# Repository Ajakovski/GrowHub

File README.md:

<div align="center">

# GrowHub - Vertical Garden

### _A highly efficient vertical plant growing garden with AI controlls for user-free handling experience._ 
  
</div>

---

# Overview

***GrowHub - Vertical Garden***

A sophisticated way of growing whatever kind of plant (only legal ones :}) from your living room, balcony, even your bedroom or wherever you want!

The idea of the project is to have a care-free environment where the user only monitors his plants from the website and we the developers are resposnible for making everything functional for healthy and low-cost plant growing.

It is a modular garden capable of supplying 1-3 floors of growing area split between 8 tiles per floor!!!

With a good team we managed to split the 4 main segments of this project accordingly which are: PCB and electrical construction, mechanical functioning of the project, server control, User-friendly and work-free experience for the customers.

---

# Motivation

In todays world a lot more people are living in flats and with the constant inflation plus the enforcment of consuming lab products a lot of people are getting restrained of consuming real, healthy and natural food.

The soil is constantly polluted due to new construction working and the constant droughts are limiting the farmers to produce enough single-ingredient food for the families in the metropolitan cities.

With those issues on mind me and my friend have come up with an idea to revolutionize the way people are getting natural ingreidents in their households.

The main goals that we want to achieve are the following:

- User-friendly and work-free experience for anyone having this product
- Highly efficiency for growing plants
- Healthy environment for both the plants and users

A lot of working skills are required for this project to succeed so i hope you understand our issues with shipping functional projects in Week 1.

---

# BOM

*Some modules are dependant based on the amount of floors accounted in the project (1-3)

_Everything is calculated for the highest amount of floors - 3_

_M = main board (×1) · F = floor board (×3) · Qty = M + 3 × F. Capacitors with no voltage listed sit on ≤ 5 V nets. Resistors are 1 % thick film, 0603 = 0.1 W, unless noted. DNP footprints and test pads are not listed._

| Designator | Function | Part | Package | Qty (3 floors) | Unit (USD) | Total (USD) | Link |
|---|---|---|---|---:|---:|---:|---|
| M: U6 | MCU module, Wi-Fi/BLE (16 MB flash, 8 MB PSRAM, U.FL antenna) | ESP32-S3-WROOM-1U-N16R8 | SMD module | 1 | $6.90 | $6.90 | [Mouser](https://www.mouser.com/en/ProductDetail/Espressif-Systems/ESP32-S3-WROOM-1U-N16R8?qs=Li%252BoUPsLEns6V0Pr5KRJtw%3D%3D) |
| M: U1 | USB D+/D− ESD protection | USBLC6-2P6 | SOT-666 | 1 | $0.65 | $0.65 | [Mouser](https://www.mouser.com/en/ProductDetail/STMicroelectronics/USBLC6-2P6?qs=6ARB0lp6jlViGcbUSvj1Mw%3D%3D) |
| M: U2 | Ambient light sensor | VEML7700-TT | SMD, 4-pin | 1 | $1.35 | $1.35 | [Mouser](https://www.mouser.com/en/ProductDetail/Vishay-Semiconductors/VEML7700-TT?qs=BcfjnG7NVaXdL6DJFdWbdw%3D%3D) |
| M: U3 | Load-cell ADC (tank mass) | NAU7802SGI | SOIC-16 | 1 | $1.87 | $1.87 | [Mouser](https://www.mouser.com/en/ProductDetail/Nuvoton/NAU7802SGI?qs=A6eO%252BMLsxmSrxisJRahwRQ%3D%3D) |
| M: U4 | Valve rail switch, current-limited | TPS27S100BPWPR | HTSSOP-14 | 1 | $3.04 | $3.04 | [Mouser](https://www.mouser.com/en/ProductDetail/Texas-Instruments/TPS27S100BPWPR?qs=0lQeLiL1qyaF4011Zes0Yg%3D%3D) |
| M: U5, U7, U9 | Floor-cable I²C buffers | PCA9600DPZ | TSSOP-8 | 3 | $6.80 | $20.40 | [Mouser](https://www.mouser.com/en/ProductDetail/NXP-Semiconductors/PCA9600DPZ?qs=Li%252BoUPsLEnu5vr2lXlgE1A%3D%3D) |
| M: U8 | Surge stopper + reverse blocking | LTC4364IS-2#PBF | SOIC-16 | 1 | $14.82 | $14.82 | [Mouser](https://www.mouser.com/en/ProductDetail/Analog-Devices/LTC4364IS-2PBF?qs=hVkxg5c3xu9riE%252B4zWkG8g%3D%3D) |
| M: U10 | Buck, 24 V → 5 V | LMR33630ADDA | HSOP-8 (exposed pad) | 1 | $3.67 | $3.67 | [Mouser](https://www.mouser.com/en/ProductDetail/Texas-Instruments/LMR33630ADDA?qs=r5DSvlrkXmL3yj62Sna%2FpQ%3D%3D) |
| M: U11 | Input current / power monitor | INA226AIDGSR | VSSOP-10 | 1 | $2.75 | $2.75 | [Mouser](https://www.mouser.com/en/ProductDetail/Texas-Instruments/INA226AIDGSR?qs=tQG3bEuiOZD4quG3egR36g%3D%3D) |
| M: U12 | Floor bus switch (I²C mux) | TCA9548APWR | TSSOP-24 | 1 | $1.65 | $1.65 | [Mouser](https://www.mouser.com/en/ProductDetail/Texas-Instruments/TCA9548APWR?qs=sGAEpiMZZMutXGli8Ay4kHAf4%2FN1WW693xDAZd3LyqA%3D) |
| F: U13 | Temperature & humidity (PTFE filter membrane) | SHT40I-AD1F-R2 | DFN-4, 1.5 × 1.5 mm | 3 | $3.06 | $9.18 | [Mouser](https://www.mouser.com/ProductDetail/Sensirion/SHT40I-AD1F-R2?qs=rQFj71Wb1eVYLTRlLwJKVQ%3D%3D) |
| F: U14, U17 | 3.3 V LDOs: logic (U17), switched sensor rail (U14) | TPS7A2033PDBVR | SOT-23-5 | 6 | $0.37 | $2.22 | [Mouser](https://www.mouser.com/en/ProductDetail/Texas-Instruments/TPS7A2033PDBVR?qs=hd1VzrDQEGjk%2FOBnRfKB4A%3D%3D) |
| F: U16 | Tray-electrode ADC | ADS1115IDGSR | VSSOP-10 | 3 | $5.19 | $15.57 | [Mouser](https://www.mouser.com/en/ProductDetail/Texas-Instruments/ADS1115IDGSR?qs=IK5e5L0zOXjKCJoVMhYO%2FQ%3D%3D) |
| F: U18 | Floor ID (1-Wire EEPROM) | DS28E07Q+T | TDFN-6, 3 × 3 mm | 3 | $2.31 | $6.93 | [Mouser](https://www.mouser.com/ProductDetail/Maxim-Integrated/DS28E07Q+T?qs=kmv/Ww32SUN5PBVtaB9uEw%3D%3D) |
| F: U19 | PWM: 4 LED channels + tray excitation | PCA9685PW,118 | TSSOP-28  (board has HVQFN-28) | 3 | $4.02 | $12.06 | [Mouser](https://www.mouser.com/ProductDetail/NXP-Semiconductors/PCA9685PW118?qs=6YAT8rHPFU%2BtfwwKq4nwEQ%3D%3D) |
| F: U20 | Floor-end cable buffer | P82B96TD,118 (NXP) | SOIC-8 | 3 | $6.15 | $18.45 | [Mouser](https://www.mouser.com/ProductDetail/NXP-Semiconductors/P82B96TD118/?qs=LOCUfHb8d9vV76HkGf93IA%3D%3D) |
| M: C11 | Load-cell ADC, VIN2P–VIN2N | C0603C331J5GACTU (330 pF, 50 V, C0G) | 0603 | 1 | $0.11 | $0.11 | [Mouser](https://www.mouser.com/c/?q=C0603C331J5GACTU) |
| M: C19 | Valve current-monitor filter | 06031F102K4T2A (1 nF, 100 V, X8R) | 0603 | 1 | $0.19 | $0.19 | [Mouser](https://www.mouser.com/en/ProductDetail/KYOCERA-AVX/06031F102K4T2A?qs=%252BdQmOuGyFcFZxL9GWikwcQ%3D%3D) |
| M: C24 | Valve-switch input, 24 V | C0603C472K5RACTU (4.7 nF, 50 V, X7R) | 0603 | 1 | $0.11 | $0.11 | [Mouser](https://www.mouser.com/c/?q=C0603C472K5RACTU) |
| M: C4, C6, C16, C18, C20, C57<br>F: C56, C64 | ADC / input filters | C0603C103K5RACTU (10 nF, 50 V, X7R) | 0603 | 12 | $0.068 | $0.82 | [Mouser](https://www.mouser.com/c/?q=C0603C103K5RACTU) |
| M: C25 | Valve rail output, 24 V | C0603C223K5RACTU (22 nF, 50 V, X7R) | 0603 | 1 | $0.12 | $0.12 | [Mouser](https://www.mouser.com/c/?q=C0603C223K5RACTU) |
| M: C13, C34, C40 | IO0 boot RC (C13), surge-stopper timer (C34), gate RC (C40) | C0603C473K1RACTU (47 nF, 100 V, X7R) | 0603 | 3 | $0.51 | $1.53 | [Mouser](https://www.mouser.com/c/?q=C0603C473K1RACTU) |
| M: C1, C5, C7, C10, C12, C15, C17, C22, C26–C28, C35, C37, C47–C50, C79–C81, C83, C84<br>F: C58, C59, C68, C70, C72, C77, C78, C85 | Decoupling, incl. the 24 V rails | C0603C104K5RACTU (100 nF, 50 V, X7R) | 0603 | 46 | $0.09 | $4.14 | [Mouser](https://www.mouser.com/c/?q=C0603C104K5RACTU) |
| M: C30, C43 | VIN / surge-stopper supply | C0805C104K1RACTU (100 nF, 100 V, X7R) | 0805 | 2 | $0.32 | $0.64 | [Mouser](https://www.mouser.com/c/?q=C0805C104K1RACTU) |
| M: C23, C32, C45 | Buck / valve-switch input caps | C0603C224K5RACTU (220 nF, 50 V, X7R) | 0603 | 3 | $0.44 | $1.32 | [Mouser](https://www.mouser.com/c/?q=C0603C224K5RACTU) |
| M: C2, C9, C14, C33, C46<br>F: C55, C60, C65, C67, C69, C71 | Decoupling / regulator VCC | C1608X7R1H105K080AB (1 µF, 50 V, X7R) | 0603 | 23 | $0.141 | $3.24 | [Mouser](https://www.mouser.com/c/?q=C1608X7R1H105K080AB) |
| F: C75, C76 | Floor 24 V entry | C0805C105K5RACTU (1 µF, 50 V, X7R) | 0805 | 6 | $0.66 | $3.96 | [Mouser](https://www.mouser.com/c/?q=C0805C105K5RACTU) |
| M: C31 | 5 V buck input, 24 V | C1210C475K5RACTU (4.7 µF, 50 V, X7R) | 1210 | 1 | $1.27 | $1.27 | [Mouser](https://www.mouser.com/c/?q=C1210C475K5RACTU) |
| M: C8, C44<br>F: C21 | Bulk, 3.3 / 5 V | C2012X7S1E106K125AE (10 µF, 25 V, X7S) | 0805 | 5 | $0.81 | $4.05 | [Mouser](https://www.mouser.com/c/?q=C2012X7S1E106K125AE) |
| M: C82 | Bulk, debug LEDs (5 V) | C1206C106K3RACTU (10 µF, 25 V, X7R) | 1206 | 1 | $1.63 | $1.63 | [Mouser](https://www.mouser.com/c/?q=C1206C106K3RACTU) |
| M: C29 | 5 V buck input, 24 V | C1210C106K5RACTU (10 µF, 50 V, X7R) | 1210 | 1 | $1.92 | $1.92 | [Mouser](https://www.mouser.com/c/?q=C1210C106K5RACTU) |
| M: C3, C38, C39, C41, C42, C51–C54 | Buck outputs, 3.3 / 5 V | CL31A226KAHNNNE (22 µF, 25 V, X5R) | 1206 | 9 | $0.81 | $7.29 | [Mouser](https://www.mouser.com/c/?q=CL31A226KAHNNNE) |
| M: C36<br>F: C73, C74 | Bulk, 24 V rail | MAL215097102E3 (220 µF, 50 V, 150 CRZ) | SMD can, 10 × 10 mm base, 17 mm tall | 7 | $2.63 | $18.41 | [Mouser](https://www.mouser.com/en/ProductDetail/Vishay-BC-Components/MAL215097102E3?qs=qmStTZH4TznNa7zgwdGJWg%3D%3D) |
| M: D1, D2, D5–D7, D17, D18, D39, D40, D42, D43<br>F: D24–D26, D45 | ESD, 3.3 V lines (load cell, leak, float, tray, OE, nRESET) | ESD5Z3.3T1G | SOD-523 | 23 | $0.144 | $3.31 | [Mouser](https://www.mouser.com/en/ProductDetail/onsemi/ESD5Z3.3T1G?qs=OSf9jACorvaH3Y8oRWEcuQ%3D%3D) |
| M: D3<br>F: D30, D31 | Pump flyback (D3), LED channel flybacks (D30, D31) | B360A-13-F (60 V, 3 A) | SMA (DO-214AC) | 7 | $0.54 | $3.78 | [Mouser](https://www.mouser.com/ProductDetail/Diodes-Incorporated/B360A-13-F?qs=sVoUGXYOGv3xoCWNHVb4bA%3D%3D) |
| M: D4, D37, D38 | Debug LEDs | Adafruit 1655 (SK6812 5050, 10-pack) | 5050 | 3 | $4.50 / 10-pack | $4.50 | [Mouser](https://www.mouser.com/ProductDetail/Adafruit/1655/?qs=GURawfaeGuATdkjqVQs49g%3D%3D) |
| M: D8, D9, D13, D14, D19, D20, D22, D41, D44<br>F: D27–D29 | ESD, 5 V cable lines (I²C, 1-Wire) | ESD5Z6.0T1G | SOD-523 | 18 | $0.096 | $1.73 | [Mouser](https://www.mouser.com/en/ProductDetail/onsemi/ESD5Z6.0T1G?qs=OSf9jACorvYUyIPFpvnErQ%3D%3D) |
| M: D16, D34–D36 | Valve flybacks (D34–D36), 5 V → 24 V reverse diode (D16) | SS16 (Taiwan Semi, 60 V, 1 A) | SMA (DO-214AC) | 4 | $0.36 | $1.44 | [Mouser](https://www.mouser.com/en/ProductDetail/Taiwan-Semiconductor/SS16?qs=JV7lzlMm3yJVXqornbcQQA%3D%3D) |
| M: D21 | Surge-stopper gate network | 1N4148W (Diotec) | SOD-123F | 1 | $0.10 | $0.10 | [Mouser](https://www.mouser.com/en/ProductDetail/Diotec-Semiconductor/1N4148W?qs=OlC7AqGiEDmsbkbAeXQtXg%3D%3D) |
| M: D23 | Input TVS | SMBJ33A (Semtech) | SMB (DO-214AA) | 1 | $0.77 | $0.77 | [Mouser](https://www.mouser.com/en/ProductDetail/Semtech/SMBJ33A?qs=jcD%2FCkGBYeN%2FjSJFT7pReg%3D%3D) |
| M: Z1, Z2 | M1/M2 gate–source Zeners (15 V) | DDZ9702T-7 | SOD-523 | 2 | $0.44 | $0.88 | [Mouser](https://www.mouser.com/ProductDetail/Diodes-Incorporated/DDZ9702T-7?qs=mQbszxtPdlMoNc/zXqSxWA%3D%3D) |
| M: F1 | Pump fuse, 3 A slow-blow | 0452003.MRL (Littelfuse NANO2 452) | NANO2, 6.1 × 2.69 mm | 1 | $2.26 | $2.26 | [Mouser](https://www.mouser.com/c/?q=0452003.MRL) |
| F: FB1 | Sensor-rail filter | BLM18PG221SN1D (220 Ω @ 100 MHz, 1.4 A) | 0603 | 3 | $0.14 | $0.42 | [Mouser](https://www.mouser.com/ProductDetail/Murata-Electronics/BLM18PG221SN1D?qs=uSeJpk%2F8In3JS43lpC2ejg%3D%3D) |
| M: IC1<br>F: U15 | 5 V drivers: LED data + pump gate (M), LED gates (F) | 74AHCT125D,118 | SOIC-14 | 4 | $0.38 | $1.52 | [Mouser](https://www.mouser.com/en/ProductDetail/Nexperia/74AHCT125D118?qs=P62ublwmbi8WxHlonNNcrA%3D%3D) |
| M: J1 | USB-C, programming / console | TE 2495155-1 | USB-C receptacle | 1 | $2.25 | $2.25 | [Mouser](https://www.mouser.com/en/ProductDetail/TE-Connectivity/2495155-1?qs=2FehpBK1j95l8dIFdQH6Ww%3D%3D) |
| M: J2 | Pump | Molex 43650-0400 | THT, 1×4, 3.00 mm, right-angle | 1 | $1.18 | $1.18 | [Mouser](https://www.mouser.com/en/ProductDetail/Molex/43650-0400?qs=A%252B%2FNCR0PvNV09lp6LzdRYg%3D%3D) |
| F: J3 | Light plate (24 V + CH1–CH4) | Molex 43650-0501 | THT, 1×5, 3.00 mm, right-angle | 3 | $2.27 | $6.81 | [Mouser](https://www.mouser.com/c/?q=43650-0501) |
| M: J4, J14, J15<br>F: J6 | Floor cable, main ↔ floor | Molex 43045-1213 | THT, 2×6, 3.00 mm, vertical | 6 | $3.08 | $18.48 | [Mouser](https://www.mouser.com/en/ProductDetail/Molex/43045-1213?qs=359VwiUTsp0cSsT%2FR1N%2Feg%3D%3D) |
| M: J5 | 24 V adapter input | Kycon KPJX-4S | 4-pin power DIN | 1 | $1.69 | $1.69 | [Mouser](https://www.mouser.com/en/ProductDetail/Kycon/KPJX-4S?qs=PGF6ObTbUZ1PHc9As62%2FZQ%3D%3D) |
| M: J8–J10 | Valves V1–V3 | Amphenol G88MPB02002C1EU | THT, 1×2, 3.00 mm, right-angle | 3 | $0.78 | $2.34 | [Mouser](https://www.mouser.com/en/ProductDetail/Amphenol-Commercial-Products/G88MPB02002C1EU?qs=%252BRAvXJslkuDOP%2FIlLZvKQA%3D%3D) |
| M: J11 | Load cell | JST B5B-PH-K-S-GW | THT, 1×5, 2.00 mm, vertical | 1 | $0.69 | $0.69 | [Mouser](https://www.mouser.com/en/ProductDetail/JST-Commercial/B5B-PH-K-S-GW?qs=cIziFXvMxOWNYlDdZstBdA%3D%3D) |
| M: J12, J13<br>F: J7 | Leak electrode (J12), float switch (J13), tray electrode (J7) | JST B2B-PH-K-M(LF)(SN) | THT, 1×2, 2.00 mm, vertical | 5 | $0.19 | $0.95 | [Mouser](https://www.mouser.com/en/ProductDetail/JST-Commercial/B2B-PH-K-MLFSN?qs=QpmGXVUTftFtjXkolasBkg%3D%3D) |
| F: J20 | Spectral light sensor | Adafruit 4698 (AS7341 breakout) | Breakout on 1×6 header | 3 | $18.95 | $56.85 | [Mouser](https://www.mouser.com/ProductDetail/Adafruit/4698?qs=DPoM0jnrROVDX4DJc6qcFQ%3D%3D) |
| M: L1 | 5 V buck inductor | Coilcraft XAL1010-822MED (8.2 µH) | SMD (XAL1010) | 1 | $5.11 | $5.11 | [Mouser](https://www.mouser.com/en/ProductDetail/Coilcraft/XAL1010-822MED?qs=zCSbvcPd3pba7AVSEX0Sqw%3D%3D) |
| M: L2 | 3.3 V buck inductor | Coilcraft XAL7070-682MEC (6.8 µH) | SMD (XAL7070) | 1 | $3.06 | $3.06 | [Mouser](https://www.mouser.com/en/ProductDetail/Coilcraft/XAL7070-682MEC?qs=zCSbvcPd3pZMktES6ULAbA%3D%3D) |
| M: PS1 | Buck, 5 V → 3.3 V | LMR33610ADDAR | HSOP-8 (exposed pad) | 1 | $2.39 | $2.39 | [Mouser](https://www.mouser.com/en/ProductDetail/Texas-Instruments/LMR33610ADDAR?qs=Cb2nCFKsA8qZzeebnoCDFA%3D%3D) |
| M: Q1–Q9<br>F: Q12, Q13 | OE/nRESET drivers (Q1–Q6), 1-Wire shifters (Q7–Q9), sensor-bus isolation (Q12, Q13) | BSS138BK,215 | SOT-23 | 15 | $0.115 | $1.73 | [Mouser](https://www.mouser.com/en/ProductDetail/Nexperia/BSS138BK215?qs=A1cBxND5mHIu7uZeHkM5Xw%3D%3D) |
| M: Q10 | Surge-stopper FET (M1) | FDB3632 | D²PAK (TO-263) | 1 | $4.92 | $4.92 | [Mouser](https://www.mouser.com/ProductDetail/ON-Semiconductor-Fairchild/FDB3632?qs=FOlmdCx%2BAA01N97Our1LAA%3D%3D) |
| M: Q11 | Reverse-blocking FET (M2) | FDMS86152 (100 V, 6 mΩ) | Power56 (5 × 6 mm) | 1 | $7.44 | $7.44 | [Mouser](https://www.mouser.com/ProductDetail/onsemi-Fairchild/FDMS86152?qs=34uu%2BPIqodzE6MPOu0Ur6w%3D%3D) |
| F: Q14, Q15 | LED channel switches CH1, CH2 | DMN4035LQ-7 | SOT-23 | 6 | $1.00 | $6.00 | [Mouser](https://www.mouser.com/ProductDetail/Diodes-Incorporated/DMN4035LQ-7?qs=EBDBlbfErPxRap3SjDUtkA%3D%3D) |
| M: Q18–Q20 | Valve switches V1–V3 (3.3 V gate drive) | SI2356DS-T1-GE3 (40 V, 70 mΩ @ 2.5 V) | SOT-23 | 3 | $0.69 | $2.07 | [Mouser](https://www.mouser.com/c/?q=SI2356DS-T1-GE3) |
| M: Q21 | Pump switch | FDMS86500L | Power56 (5 × 6 mm) | 1 | $4.19 | $4.19 | [Mouser](https://www.mouser.com/en/ProductDetail/onsemi/FDMS86500L?qs=unG0t268Z%2FHjzOt5KnlSWw%3D%3D) |
| M: R70 | Input current shunt (U8 + U11) | WSK25125L000FEA (5 mΩ, 1 %, 1 W, 4-terminal) | 2512, Kelvin | 1 | $2.99 | $2.99 | [Mouser](https://www.mouser.com/c/?q=WSK25125L000FEA) |
| M: R5, R6 | USB D+/D− links | RC0603JR-070RL (0 Ω) | 0603 | 2 | $0.10 | $0.20 | [Mouser](https://www.mouser.com/c/?q=RC0603JR-070RL) |
| M: R17, R67, R91, R92 | M1 gate series, U2 supply filter, U11 input filter | RC0603FR-0710RL (10 Ω) | 0603 | 4 | $0.12 | $0.48 | [Mouser](https://www.mouser.com/c/?q=RC0603FR-0710RL) |
| F: R111, R112 | LED gate resistors | RC0603FR-0733RL (33 Ω) | 0603 | 6 | $0.12 | $0.72 | [Mouser](https://www.mouser.com/c/?q=RC0603FR-0733RL) |
| M: R22 | Debug-LED data series | RC0603FR-0747RL (47 Ω) | 0603 | 1 | $0.12 | $0.12 | [Mouser](https://www.mouser.com/c/?q=RC0603FR-0747RL) |
| M: R13, R14, R81, R119–R121 | Load-cell filter, valve gate series, U8 gate RC | RC0603FR-07100RL (100 Ω) | 0603 | 6 | $0.12 | $0.72 | [Mouser](https://www.mouser.com/ProductDetail/YAGEO/RC0603FR-07100RL?qs=sGAEpiMZZMtNwx8wKGcP0iiifGQW6WGa) |
| M: R25 | Pump gate series | RC0603FR-07220RL (220 Ω) | 0603 | 1 | $0.12 | $0.12 | [Mouser](https://www.mouser.com/c/?q=RC0603FR-07220RL) |
| M: R43 | Valve current-monitor divider | RC0603FR-07820RL (820 Ω) | 0603 | 1 | $0.12 | $0.12 | [Mouser](https://www.mouser.com/c/?q=RC0603FR-07820RL) |
| M: R26, R32, R35–R39, R54, R63, R133<br>F: R103 | ADC/input series, 1-Wire pull-ups (5 V), U8 supply feed | RC0603FR-071KL (1 kΩ) | 0603 | 13 | $0.017 | $0.22 | [Mouser](https://www.mouser.com/c/?q=RC0603FR-071KL) |
| M: R140–R145 | OE/nRESET drain resistors (survive a cable short to 24 V) | RC2010FK-071KL (1 kΩ, 0.75 W) | 2010 | 6 | $0.13 | $0.78 | [Mouser](https://www.mouser.com/c/?q=RC2010FK-071KL) |
| M: R41 | Valve current-monitor divider | RC0603FR-071K2L (1.2 kΩ) | 0603 | 1 | $0.12 | $0.12 | [Mouser](https://www.mouser.com/c/?q=RC0603FR-071K2L) |
| M: R52, R53, R64, R65, R76, R77<br>F: R104, R106 | Floor-cable I²C pull-ups to 5 V | RC0603FR-072K2L (2.2 kΩ) | 0603 | 12 | $0.017 | $0.20 | [Mouser](https://www.mouser.com/c/?q=RC0603FR-072K2L) |
| M: R4, R9, R40, R42, R51, R84, R85<br>F: R109, R110 | I²C pull-ups, float pull-up, U4 enable / diagnostics | RC0603FR-074K7L (4.7 kΩ) | 0603 | 13 | $0.017 | $0.22 | [Mouser](https://www.mouser.com/c/?q=RC0603FR-074K7L) |
| M: R45 | U4 current-limit set | RC0603FR-074K87L (4.87 kΩ) | 0603 | 1 | $0.10 | $0.10 | [Mouser](https://www.mouser.com/c/?q=RC0603FR-074K87L) |
| M: R74 | U8 output-clamp divider (≈ 30 V) | RC0603FR-074K99L (4.99 kΩ) | 0603 | 1 | $0.12 | $0.12 | [Mouser](https://www.mouser.com/c/?q=RC0603FR-074K99L) |
| M: R15, R23 | USB-C CC pull-downs | RC0603FR-075K1L (5.1 kΩ) | 0603 | 2 | $0.12 | $0.24 | [Mouser](https://www.mouser.com/c/?q=RC0603FR-075K1L) |
| M: R34 | VIN sense divider | RC0603FR-075K6L (5.6 kΩ) | 0603 | 1 | $0.12 | $0.12 | [Mouser](https://www.mouser.com/c/?q=RC0603FR-075K6L) |
| M: R60 | U8 UV/OV divider | RC0603FR-076K04L (6.04 kΩ) | 0603 | 1 | $0.12 | $0.12 | [Mouser](https://www.mouser.com/c/?q=RC0603FR-076K04L) |
| M: R28 | Valve-rail sense divider | RC0603FR-078K2L (8.2 kΩ) | 0603 | 1 | $0.12 | $0.12 | [Mouser](https://www.mouser.com/c/?q=RC0603FR-078K2L) |
| M: R3, R16, R21, R24, R29–R31, R61, R80, R82, R88–R90, R95, R96, R131, R134–R139<br>F: R99, R105, R125, R126 | Pull-ups, pull-downs, gate series | RC0603FR-0710KL (10 kΩ) | 0603 | 34 | $0.017 | $0.58 | [Mouser](https://www.mouser.com/ProductDetail/YAGEO/RC0603FR-0710KL?qs=grNVn54RoB%2B3GtjbJj3wJQ%3D%3D) |
| M: R48 | Valve-rail bleed (24 V) | ERJ-PA3F1002V (10 kΩ, 1/3 W) | 0603 | 1 | $0.15 | $0.15 | [Mouser](https://www.mouser.com/c/?q=ERJ-PA3F1002V) |
| M: R46, R47, R55, R56, R68, R69 | Mux channel pull-ups, floors 1–3 | RC0603FR-0722KL (22 kΩ) | 0603 | 6 | $0.12 | $0.72 | [Mouser](https://www.mouser.com/c/?q=RC0603FR-0722KL) |
| M: R79 | 5 V buck feedback | RC0603FR-0724K9L (24.9 kΩ) | 0603 | 1 | $0.12 | $0.12 | [Mouser](https://www.mouser.com/c/?q=RC0603FR-0724K9L) |
| M: R94 | 3.3 V buck feedback | RC0603FR-0743K2L (43.2 kΩ) | 0603 | 1 | $0.12 | $0.12 | [Mouser](https://www.mouser.com/c/?q=RC0603FR-0743K2L) |
| F: R96 | nRESET pull-up / sensor-rail enable | RC0603FR-0747KL (47 kΩ) | 0603 | 3 | $0.12 | $0.36 | [Mouser](https://www.mouser.com/c/?q=RC0603FR-0747KL) |
| M: R10–R12, R18–R20, R27, R33, R44, R66, R75, R78, R83, R93, R97, R122–R124, R132<br>F: R101, R113, R114, R127–R130 | Gate pull-downs, divider and feedback tops, enables | RC0603FR-07100KL (100 kΩ) | 0603 | 40 | $0.017 | $0.68 | [Mouser](https://www.mouser.com/ProductDetail/YAGEO/RC0603FR-07100KL?qs=e1ok2LiJcmaihem8Va5%2Fsw%3D%3D) |
| M: R73 | U8 output-clamp divider (≈ 30 V) | RC0603FR-07115KL (115 kΩ) | 0603 | 1 | $0.12 | $0.12 | [Mouser](https://www.mouser.com/c/?q=RC0603FR-07115KL) |
| M: R59 | U8 UV/OV divider | RC0603FR-07243KL (243 kΩ) | 0603 | 1 | $0.12 | $0.12 | [Mouser](https://www.mouser.com/c/?q=RC0603FR-07243KL) |
| M: R62 | U8 shutdown pull-up | RC0603FR-071ML (1 MΩ) | 0603 | 1 | $0.12 | $0.12 | [Mouser](https://www.mouser.com/c/?q=RC0603FR-071ML) |
| M: SW1, SW2 | Reset / boot buttons | E-Switch TL3342 obsolete, not sold by Mouser: leave unfitted | 5.2 × 5.2 mm SMD | 2 | — | — | — |
| **Total** |  |  |  |  |  | **$332.04** |  |

*Notice: These shipping costs are for a Balkan country so if youa re from EU or USA there are very high chances of having lower shipping costs*

*Notice: These are just recommendations that i have found to be secure and hopefully the cheapest possible option available. Do your onw research if you think that better deals exist on the current market depending on when you are buing it*.

---

# Features 

- **High Efficiency** - Greater production compared to normal gardening
- **Water Saving** - Lower consumption through optimised watering systems
- **Small occupation of space** - The vertical trait makes it suitable for homes
- **Care-Free Product** - Everything is automated
- **User friendly** - No need of gardening expertise to start

---

# PCB Design

The PCB was designed specifically for this project and its layout.

Key concepts of the design:
- 4 layer on main PCB
- Work is split on two PCBs
- GND Plane on L2 for return path
- GND Fill on L1,L3,L4 for signal integrity
- Power Fills for certain areas of L3
- Protection circuits and components for safety

## PCB Layout

### Main PCB

_*Some pictures may have been distorted in order to fit them in the README.*

### Floor PCB

---
 
## Schematic

***Refer to the PDF file for better overview*** [PDF](Documentation/GrowHub_Elec.pdf)

### Main Schematic

#### Main Floor Schematic

#### Board IO Schematic

### Floor Schematic

## Components Placement

<div align="center">

### Main PCB

### Floor PCB

</div>

---

# Assembly Guide

## Hardware

***A visual representation of the whole project has been provided within repository files***

```
Hardware/FULLY_ASSEMBLED_PROJECT.step
```

### 1. Order the PCBs and 3D Model

Navigate to: (For PCBs)

```bash
Hardware/KiCad/Gerbers/
```

Some files are in zip files due to github memory restrictions.

*Upload the G-Code files to your preferred manufacturer and order the parts.*

### 2. Order the Components

Whether you want to order it trough PCBA or solder it manually you should refer to the BOM file.

```bash
Hardware/BOM.csv
```

I recommend getting PCBA or sorting them out before you start assembling because this is a big project with loads of components.

### 3. Soldering Process

I highly suggest using oven reflow or hot pad soldering for the SMD whether you have decided to assemble it yourself.

Solder in regions if you use a smaller heating plate and always double check how you place the components.

Place larger modules first and then every passive peripheral components.

Some soldering might require a soldering iron due to L1 fill and heat dissipation in the copper.

Recommended tools are:
- FLux
- Reflow soldering oven or Heating plate for soldering
- Tweezers for placing the components
- Solder paste
- Helping hands with a magnifying glass would be wonderfull

### 4. Assemble the PCBs in the Enclosure

***Materials needed for assembling:***

- 16x m3 Screw nuts (if you install main board +3 floor boards)
- Other screws should come with the designated components.

***Steps for assembling***

On the part with the PCB assembling you really just need to screw them in place and thats it. 4 m3 screw nuts and a good place for the external antenna.

How to assemble the 3D model:

The 3D prints arrive ready for stacking. There is no manual work needed and the latches for the PCBs are easy to mount on. The floors stack on top of each other safely so that they dont fall off so easily.

---

# Software

Everything lives under `Software/website`. Compose brings up **backend**, **AI**, **nginx frontend**, and an optional **simulator**.

### Stack

| Piece | Location | Notes |
|---|---|---|
| Frontend | `frontend/` | Static HTML/CSS/JS (landing, how-it-works, shop, demo, login, dashboard) |
| Nginx | `nginx.conf` | Serves the site on `:5000` and proxies `/api/` → backend (same-origin cookies) |
| Backend | `backend/` | FastAPI on `:8000` — auth, web dashboard APIs, device ingest, AI status/controls |
| AI | `ai/` | FastAPI on `:8001` — chat + reviews; talks to the backend with `GROWHUB_AI_KEY` |
| Database | SQLite | Accounts, sessions, hub history / plants / camera source / AI summaries |
| Simulator | `backend/esp32_simulator.py` | Fake hub telemetry + optional OpenCV webcam frames |

### Product surfaces

- **Landing** (`index.html`) — product story and contact
- **How it works** — AI care explainer + path into the demo
- **Catalog** (`shop.html`) — Hub / planter tile / stack modules from `/api/web/tiles`
- **Live demo** (`demo.html`) — `POST /api/auth/demo` guest session, then dashboard
- **Login / verify** — email + password; verification via Resend or backend log when unset
- **Dashboard** — plant stats, history (1h / 24h / 7d), camera (webcam or stock images), AI chat, plant picker  
  Guest sessions can **view** the shared hub but cannot change plants, camera source, or actuators via AI

### What the backend tracks

- Hub + per-tile telemetry: water temp / heater, EC, pH, reservoir level, air temp, humidity, light, flow
- Offline detection from report cadence (missed reports → hub offline UI)
- Sustained alerts (pH out of range, low/no flow, low water, cold water) — noisy single readings do not fire
- Actuator modes for lights / pump / heater (`auto` | `on` | `off`), returned to devices on the next telemetry cycle
- Camera frames in memory only (size-capped uploads); optional stock image folder for demos without a webcam
- Shared SQLite history (averaged charts, ~7 day retention)

### How to run (Docker, recommended)

From `Software/website`:

```bash
cp .env.example .env   # optional; fill LLM / email / secrets for a fuller setup
docker compose up -d --build
```

| URL | What |
|---|---|
| http://localhost:5000/ | Marketing site |
| http://localhost:5000/demo.html | Guest demo entry |
| http://localhost:5000/dashboard.html | Dashboard (login or demo) |
| http://localhost:8000/ | Backend API (direct; prefer `:5000/api/` from the browser) |
| http://localhost:8001/ | AI service |

```bash
docker compose down        # keep SQLite volume
docker compose down -v     # wipe growhub-data
```

The simulator mounts `/dev/video0`. Remove the `devices:` block in `compose.yaml` if you have no camera.

### How to run (manual)

1. Backend: from `Software/website/backend`, `uvicorn main:app --reload --port 8000`
2. Frontend: either nginx with `nginx.conf`, or temporarily `python -m http.server 5000` from `frontend/` (API calls should still hit the same origin or set `GROWHUB_API_ORIGIN`)
3. AI (optional): from `Software/website/ai`, run its uvicorn entry on `8001` with `GROWHUB_API_BASE` and keys set
4. Simulator: `python esp32_simulator.py` (needs `GROWHUB_DEVICE_KEY` matching the backend)

### Environment (high level)

Copy `Software/website/.env.example` → `.env`. Important knobs:

| Variable | Purpose |
|---|---|
| `GROWHUB_DEVICE_KEY` | Required for device ingest (unset → rejected unless `GROWHUB_ALLOW_INSECURE_DEVICE=1`) |
| `GROWHUB_AI_KEY` | Shared secret for AI ↔ backend status/controls and AI-key dashboard reads |
| `GROWHUB_TRUST_PROXY` | `1` in compose so rate limits use nginx `X-Real-IP` / `X-Forwarded-For` |
| `GROWHUB_COOKIE_SECURE` | `1` when serving HTTPS |
| `GROWHUB_WEB_ORIGIN_REGEX` | Allowed browser origins for cookies/CORS (default: localhost + LAN) |
| `LLM_API_KEY` / `LLM_BASE_URL` / `LLM_MODEL` | OpenAI-compatible provider for chat + reviews |
| `RESEND_API_KEY` / `GROWHUB_EMAIL_FROM` | Verification + contact email (empty → log verification links) |
| `GROWHUB_PUBLIC_URL` | Absolute base for verification links in production |

### Useful API routes

| Method | Path | Purpose |
|---|---|---|
| POST | `/api/auth/register` · `/login` · `/demo` · `/logout` | Accounts + guest demo |
| GET | `/api/auth/me` | Current user (`email`, `is_demo`) |
| GET | `/api/web/plant-stats` | Dashboard snapshot (auth or AI key) |
| GET | `/api/web/history?device=…&range=1h` | Chart history |
| PUT | `/api/web/plants` · `/camera-source` | Hub config (**non-demo users only**) |
| GET | `/api/web/camera` · `/camera/stream` | Still / MJPEG |
| POST | `/api/web/contact` | Contact form (honeypot + rate limit) |
| POST | `/api/device/telemetry` · `/camera` | Device ingest (`X-Device-Key`) |
| GET/PUT | `/api/ai/controls` | Actuator modes (`X-AI-Key`) |
| POST | AI `:8001/chat` · `/review` | Logged-in chat / on-demand review |

### Tests

From `Software/website/backend` (with `requirements-dev.txt` installed):

```bash
python -m pytest tests/ -q
```

Covers demo/auth, web API, security guards (demo read-only, device fail-closed, upload cap, proxy IP), and static frontend/nginx contracts.

### Deploy notes

For anything beyond local compose: use strong secrets (not the `dev-*-key` defaults), set `GROWHUB_COOKIE_SECURE=1` on HTTPS, prefer exposing only `:5000` (or your TLS terminator) rather than publishing `:8000` / `:8001`, and keep `GROWHUB_TRUST_PROXY` aligned with whether a reverse proxy sits in front of the backend.

---

# Firmware

ESP-IDF firmware for the Hub MCU lives under **Firmware/firmware**. Target is the **ESP32-S3-WROOM-1U-N16R8** (16 MB flash, 8 MB octal
PSRAM) matching the main board.

### Status

Scaffolding is in place; this is **not** a finished production image yet. `app_main` currently logs a start line. Actuator control,
safe-state latching, and a USB bench console are implemented to bring up and exercise the nine FW-27 actuator pins on real hardware
or a DevKit.

### Layout

| Path | Role |
|---|---|
| `main/main.c` | ESP-IDF entry (`app_main`) |
| `main/board.h` + `Kconfig.projbuild` | Pin map + board variant (`GROWHUB_REV_A` or `BENCH_DEVKITC1`) |
| `main/actuators*.{c,h}` | Valve / pump / dose-select / OE / nRESET API, latching faults, pin reports |
| `main/safe_state.c` | Drive actuator pins low and latch untill reboot |
| `main/bench_cosnole.c` | USB console commands for pin dump, valve open/close, safe, restart |
| `main/hw_if/` + `hw_*_esp.c` | Thin hardware interface (pins, time, lock, system) |
| `sdkconfig.defaults` | ESP32-S3 + 16 MB flash + octal PSRAM defaults |
| `sdkconfig.bench` | Extra config overlay for DevKit bench work |
| `partitions.csv` | Partition table |

### Build (ESP-IDF)

Needs a normal ESP-IDF environment with `IDF_PATH` set (ESP-IDF v5.x recommended).

```bash
cd Firmware/firmware
idf.py set-target esp32s3
# Pick a board variant in menuconfig - GrowHub board
idf.py menuconfig
idf.py build
idf.py -p /dev/ttyUSB0 flash monitor  # adjust port as needed
```

For bench bring-up on a DevKit, use the `BENCH_DEVKITC1` Kconfig choice (and `sdkconfig.bench` where helpful). On the real Hub PCB, use
`GROWHUB_REV_A`.

### What works today vs next

**In tree now**

- Actuator boot latch + init / safe-state
- Valve open/close and pump on/off with refusal reasons (busy, another valve, pin fault, ...)
- Bench console over USB for manual pin checks

**Still to do**

- Sensors, floor bus, networking, and posting telemetry/camera to `/api/device*`
- Applying dashboard/AI control modes (`lights` / `pump` / `heater`) from the backend response

Untill the device firmware talks to the cloud API, use the **website simulator** (`esp32_simulator.py` in Compose) to drive the dashboard.

---

# Current Status

- [X] Initial Concept
- [X] Component List
- [X] Schematic Layout Main PCB
- [X] PCB Design Main PCB
- [X] Schematic Layout Floor PCB
- [X] PCB Design Floor PCB
- [X] Firmware (ESP-IDF scaffolding + actuators / bench console; sensors & cloud link still open)
- [X] Software (website, guset demo, AI, tests, docker)
- [X] Final BOM
- [X] Create a Zine (if needed)
- [X] Functional build
- [ ] Add more sensors
- [ ] Lower BOM costs
- [ ] v2.0 Build

---

# Creators

### Ajakovski - Hardware and PCB Design

### soggy8 - 3D Design and Software

# License

This project is licensed under the **MIT License** - see [LICENSE](LICENSE) for full terms.

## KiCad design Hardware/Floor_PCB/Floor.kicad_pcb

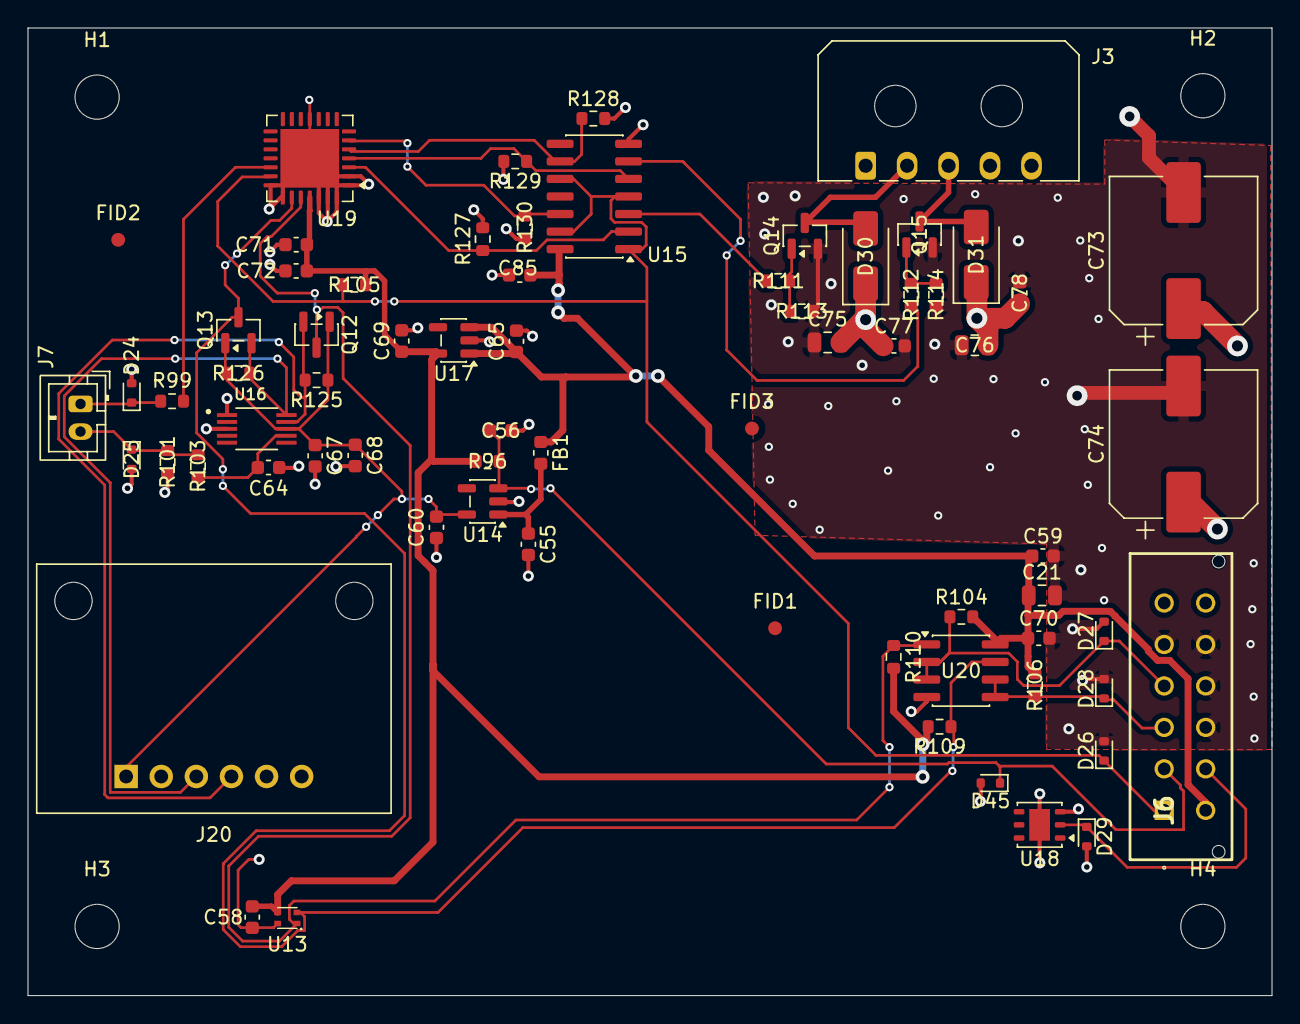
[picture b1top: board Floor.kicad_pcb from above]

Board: 2 copper layers, 90.0 x 70.0 mm, 73 parts (0 on the bottom side), 29 nets.

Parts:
C21: 10uF; C_0805_2012Metric
C55, C60, C65, C67, C69, C71: 1uF; C_0603_1608Metric
C56, C64: 10nF; C_0603_1608Metric
C58, C59, C68, C70, C72, C77, C78, C85: 100nF; C_0603_1608Metric
C73, C74: 220uF; CP_Elec_10x10.5
C75, C76: 1uF; C_0805_2012Metric
D24, D25, D26, D45: ESD5Z3.3T1G; D_SOD-523
D27, D28, D29: ESD5Z6.0T1G; D_SOD-523
D30, D31: SS25; D_SMA
FB1: Ferrite 0603 (or 0R); L_0603_1608Metric
FID1, FID2, FID3: Fiducial; Fiducial_1mm_Mask2mm
H1, H2, H3, H4: M3; MountingHole_3.2mm_M3
J3: Light plate (Micro-Fit 1x5); Molex_Micro-Fit_3.0_43650-0500_1x05_P3.00mm_Horizontal
J6: Micro-Fit 3.0 2x6 (43045-1213); 0430451213
J7: Tray electrode (JST PH 2p); JST_PH_B2B-PH-K_1x02_P2.00mm_Vertical
J20: AS7341 breakout (Adafruit 4698); Adafruit_4698_AS7341_Breakout
Q12, Q13: BSS138BK-215; SOT-23
Q14, Q15: DMN4035L-7; SOT-23
R96: 47K; R_0603_1608Metric
R99, R105, R125, R126: 10K; R_0603_1608Metric
R101, R113, R114, R127, R128, R129, R130: 100K; R_0603_1608Metric
R103: 1K; R_0603_1608Metric
R104, R106: 2.2K; R_0603_1608Metric
R109, R110: 4.7K; R_0603_1608Metric
R111, R112: 33; R_0603_1608Metric
U13: SHT4XI-DIGITAL
U14, U17: TPS7A2033PDBVR; SOT-23-5
U15: 74AHCT125; SOIC-14_3.9x8.7mm_P1.27mm
U16: ADS1115IDGSR; SOP50P490X110-10N
U18: DS28E07Q_T; Maxim_TDFN-6-1EP_3x3mm_P0.95mm_EP1.5x2.3mm
U19: PCA9685BS_118; QFN-28-1EP_6x6mm_P0.65mm_EP4.25x4.25mm
U20: P82B96D; SOIC-8_3.9x4.9mm_P1.27mm

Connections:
1-Wire_X: D29.1 (K), J6.8 (1-WIRE), U18.2 (IO)
5V_SENS: C55.1, FB1.2, U14.1 (IN)
+3V3: C58.2, C69.1, C71.1, C72.1, R96.2, R105.1, R109.2, R110.2, U13.3 (VDD), U17.5 (OUT), U19.25 (VDD)
+3V3_SENS: C60.1, C67.1, C68.1, J20.1, Q12.1 (G), Q13.1 (G), R125.1, R126.1, U14.5 (OUT), U16.8 (VDD)
+5V: C21.1, C59.1, C65.1, C70.1, C85.1, FB1.1, J6.7 (+5V), R104.2, R106.2, U15.14 (VCC), U17.1 (IN), U17.3 (EN), U20.8 (VCC)
+24V: C73.1, C74.1, C75.2, C76.2, C77.1, C78.1, D30.1 (K), D31.1 (K), J3.1, J6.6 (+24V), J6.12 (+24V)
CH1: R127.1, U15.2, U19.3 (LED0)
CH1_G: R111.1, U15.3
CH2: R129.1, U15.5, U19.4 (LED1)
CH2_G: R112.1, U15.6
CH3: R128.1, U15.9, U19.5 (LED2)
CH4: R130.1, U15.12, U19.6 (LED3)
GND: C21.2, C55.2, C56.2, C58.1, C59.2, C60.2, C64.2, C65.2, C67.2, C68.2, C69.2, C70.2, C71.2, C72.2, C73.2, C74.2, C75.1, C76.1, C77.2, C78.2, C85.2, D24.2 (A), D25.2 (A), D26.2 (A), D27.2 (A), D28.2 (A), D29.2 (A), D45.2 (A), J6.5 (GND), J6.9 (GND), J6.10 (GND), J6.11 (GND), J20.2, Q14.2 (S), Q15.2 (S), R101.1, R113.2, R114.2, R127.2, R128.2, R129.2, R130.2, U13.4 (VSS), U14.2 (GND), U15.7 (GND), U16.1 (ADDR), U16.3 (GND), U17.2 (GND), U18.3 (GND), U18.7 (EP), U19.1 (A3), U19.2 (A4), U19.11 (VSS), U19.21 (A5), U19.22 (EXTCLK), U19.26 (A0), U19.27 (A1), U19.28 (A2), U19.29 (EXP), U20.4 (GND)
unnamed: Q14.1 (G), R111.2, R113.1
unnamed: Q15.1 (G), R112.2, R114.1
unnamed: C64.1, R103.1, U16.7 (AIN3)
OE_X: D26.1 (K), J6.1 (OE), R105.2, U15.1, U15.4, U15.10, U15.13, U19.20 (~OE)
R_LED-: D31.2 (A), J3.3, Q15.3 (D)
SCL_S: J20.3, Q13.2 (S), R126.2, U16.10 (SCL)
SCL_X: Q13.3 (D), R109.1, U13.2 (SCL), U19.23 (SCL), U20.7 (SY)
SC_X: D28.1 (K), J6.3 (SCL), R106.1, U20.5 (TY), U20.6 (RY)
SDA_S: J20.4, Q12.2 (S), R125.2, U16.9 (SDA)
SDA_X: Q12.3 (D), R110.1, U13.1 (SDA), U19.24 (SDA), U20.1 (SX)
SD_X: D27.1 (K), J6.4 (SDA), R104.1, U20.2 (RX), U20.3 (TX)
TRAY_A: D24.1 (K), J7.1, R99.2
TRAY_B: D25.1 (K), J7.2, R101.2, R103.2
TRAY_EXC: R99.1, U19.19 (LED15)
W_LED-: D30.2 (A), J3.2, Q14.3 (D)
nRESET_X: C56.1, D45.1 (K), J6.2 (nRESET), R96.1, U14.3 (EN)
